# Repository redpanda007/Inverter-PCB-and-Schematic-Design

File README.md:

# Inverter PCB and Schematic Design

This project contains the PCB and schematic design for an inverter.

## Project Overview

The project includes:
- Schematic diagram of the inverter
- PCB design for the inverter
- 3D PCB design

## Schematic Diagram

The schematic diagram for this inverter can be viewed online at:
[https://a360.co/3YYau8m](https://a360.co/3YYau8m)

## PCB Design

The PCB design for this inverter can be viewed online at:
[https://a360.co/4dPXrd1](https://a360.co/4dPXrd1)

## 3D PCB Design

A 3D view of the PCB design can be accessed at:
[https://a360.co/3TpDP8b](https://a360.co/3TpDP8b)

## Viewing the Designs

To view the schematic, PCB designs, and 3D PCB model, click on the links provided above. These will take you to online viewers where you can interact with the designs.

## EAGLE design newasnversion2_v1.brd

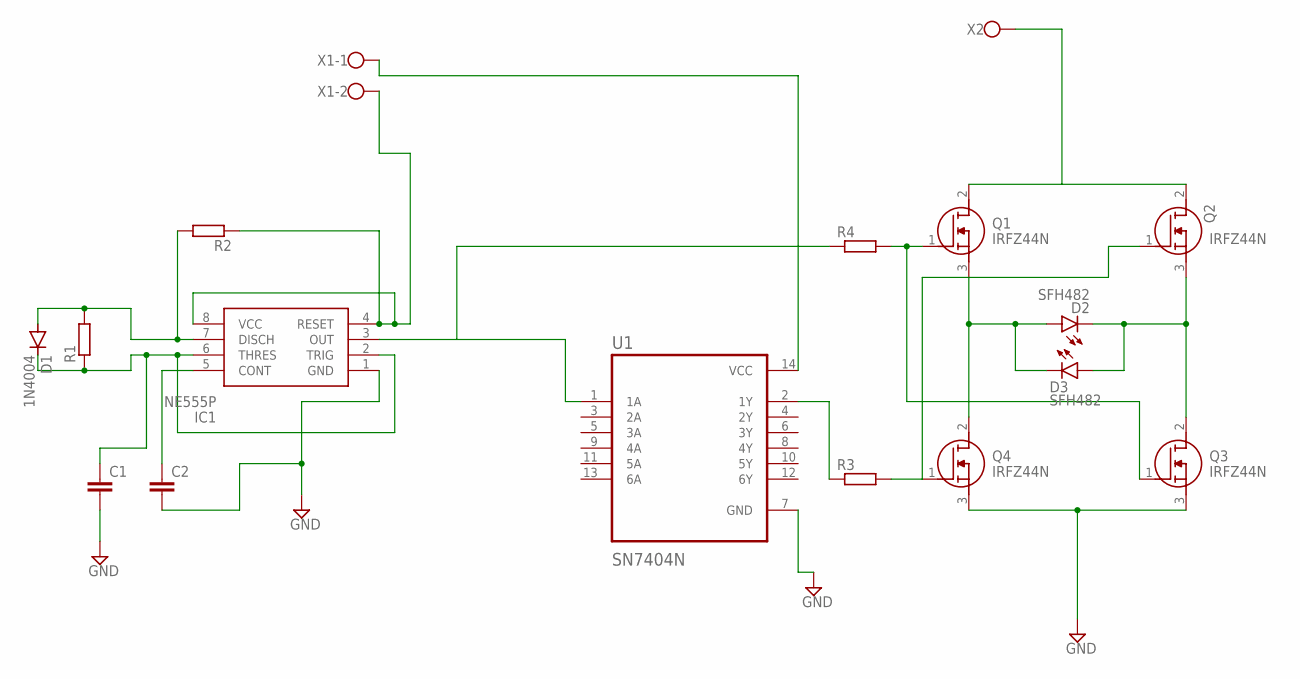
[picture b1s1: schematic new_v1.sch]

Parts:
C1, C2: C-EU025-030X050; C025-030X050
D1: 1N4004; DO41-10
D2, D3: SFH482
IC1: NE555P; DIP794W53P254L959H508Q8N
Q1, Q2, Q3, Q4: IRFZ44N; TO254P440X1000X1900-3P
R1, R2, R3, R4: R-EU_0207/7; 0207/7
U1: SN7404N; DIP794W45P254L1969H508Q14
X1: W237-102
X2: W237-112

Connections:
GND: C1.2, C2.2, IC1.1 (GND), Q3.3 (S), Q4.3 (S), U1.7 (GND)
unnamed: Q1.1 (G), Q3.1 (G), R4.2
unnamed: C2.1, IC1.5 (CONT)
unnamed: D1.A, IC1.7 (DISCH), R1.2, R2.2
unnamed: C1.1, D1.C, IC1.2 (TRIG), IC1.6 (THRES), R1.1
unnamed: IC1.4 (RESET), IC1.8 (VCC), R2.1, X1.2
unnamed: Q1.2 (D), Q2.2 (D), X2.1
unnamed: U1.14 (VCC), X1.1
unnamed: IC1.3 (OUT), R4.1, U1.1 (1A)
unnamed: Q2.1 (G), Q4.1 (G), R3.2
unnamed: D2.K (C), D3.A, Q2.3 (S), Q3.2 (D)
unnamed: D2.A, D3.K (C), Q1.3 (S), Q4.2 (D)
unnamed: R3.1, U1.2 (1Y)

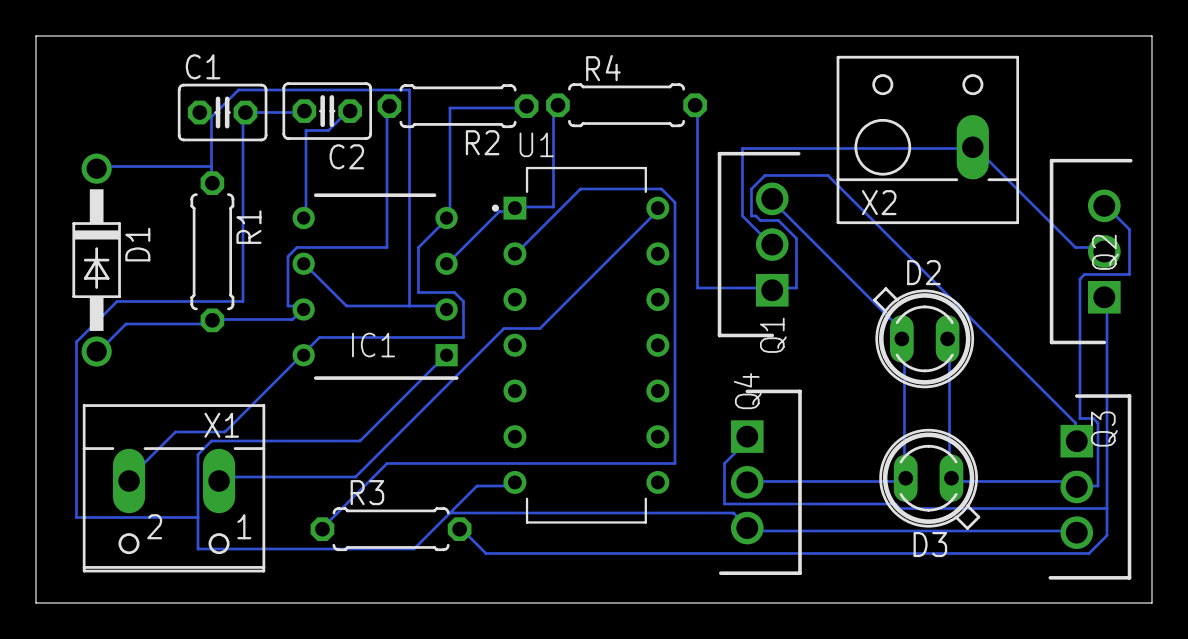
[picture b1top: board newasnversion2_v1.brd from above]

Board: 2 copper layers, 62.0 x 31.5 mm, 17 parts (0 on the bottom side), 13 nets.
